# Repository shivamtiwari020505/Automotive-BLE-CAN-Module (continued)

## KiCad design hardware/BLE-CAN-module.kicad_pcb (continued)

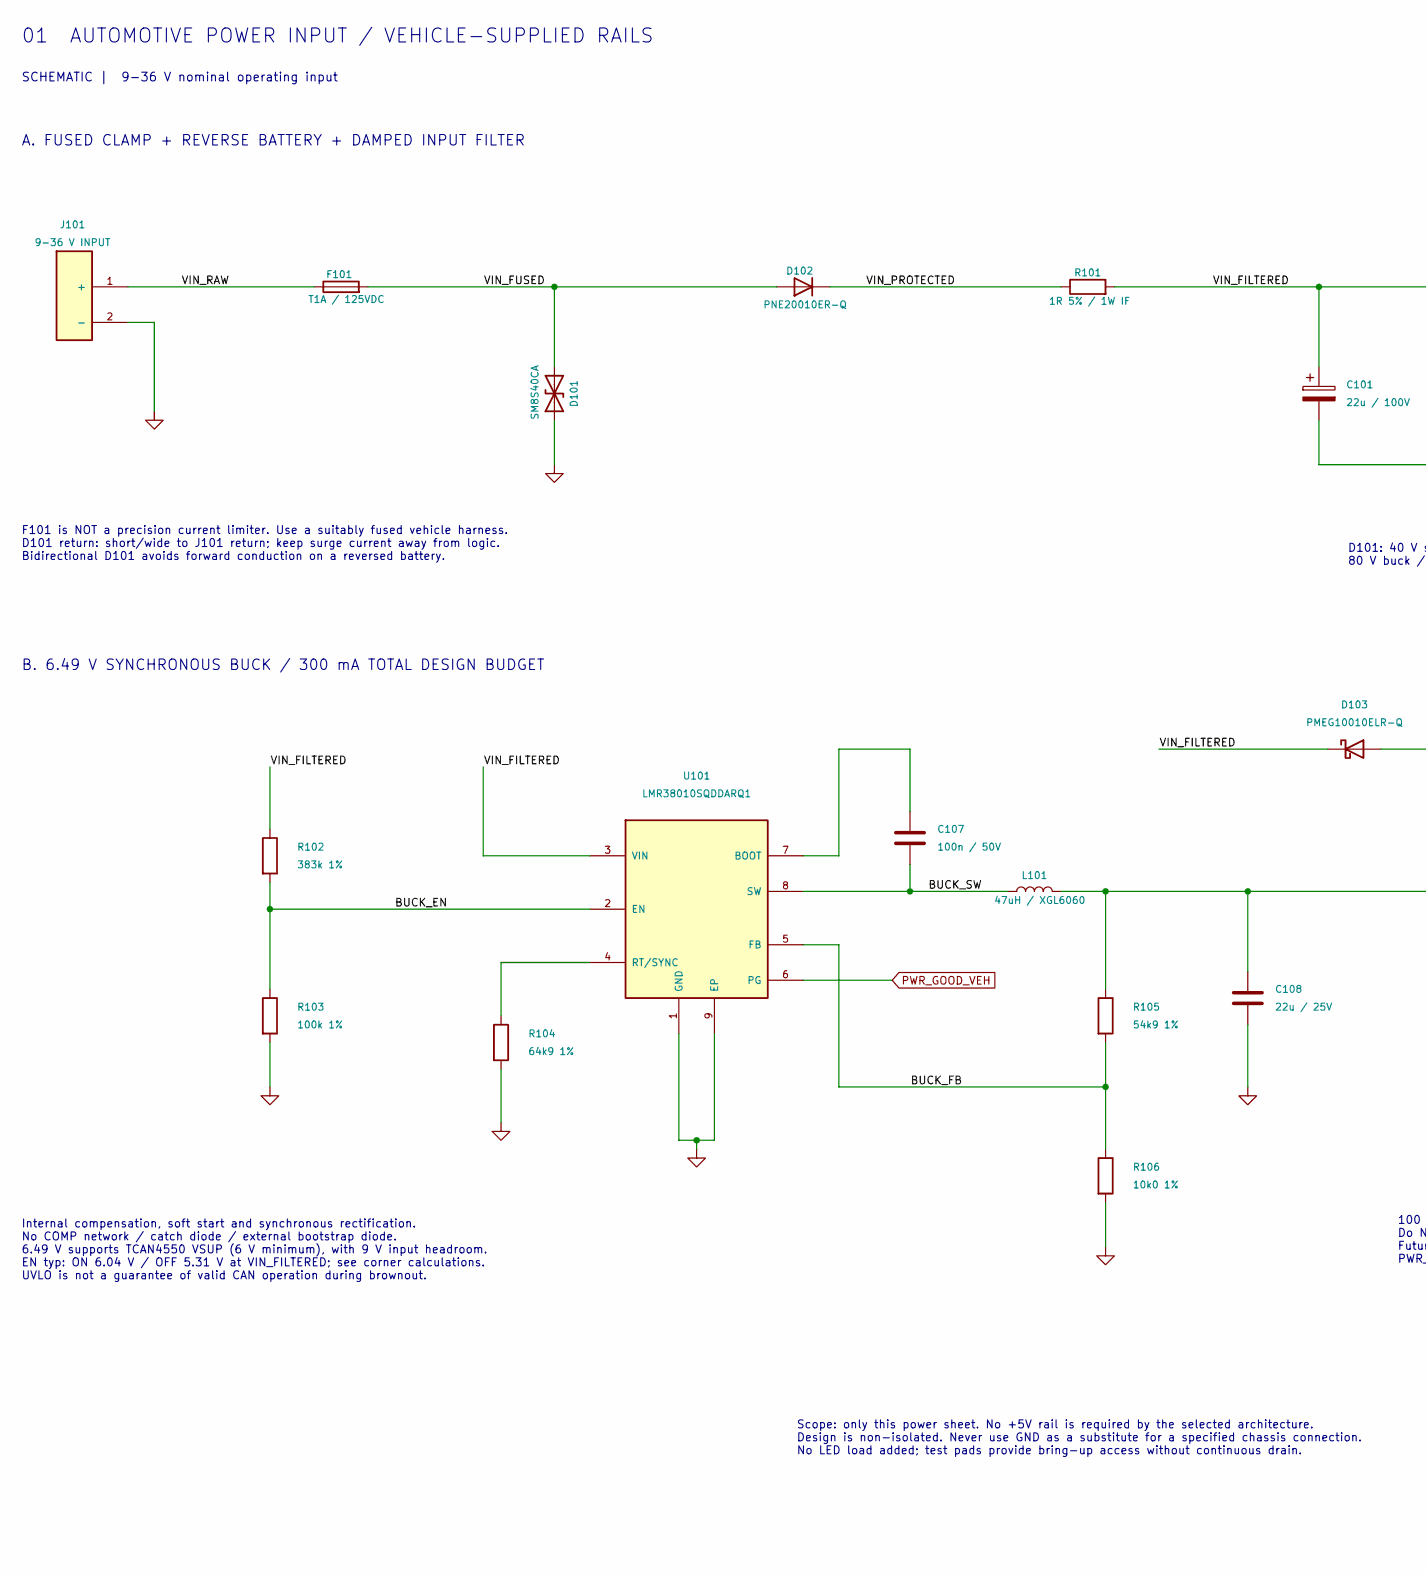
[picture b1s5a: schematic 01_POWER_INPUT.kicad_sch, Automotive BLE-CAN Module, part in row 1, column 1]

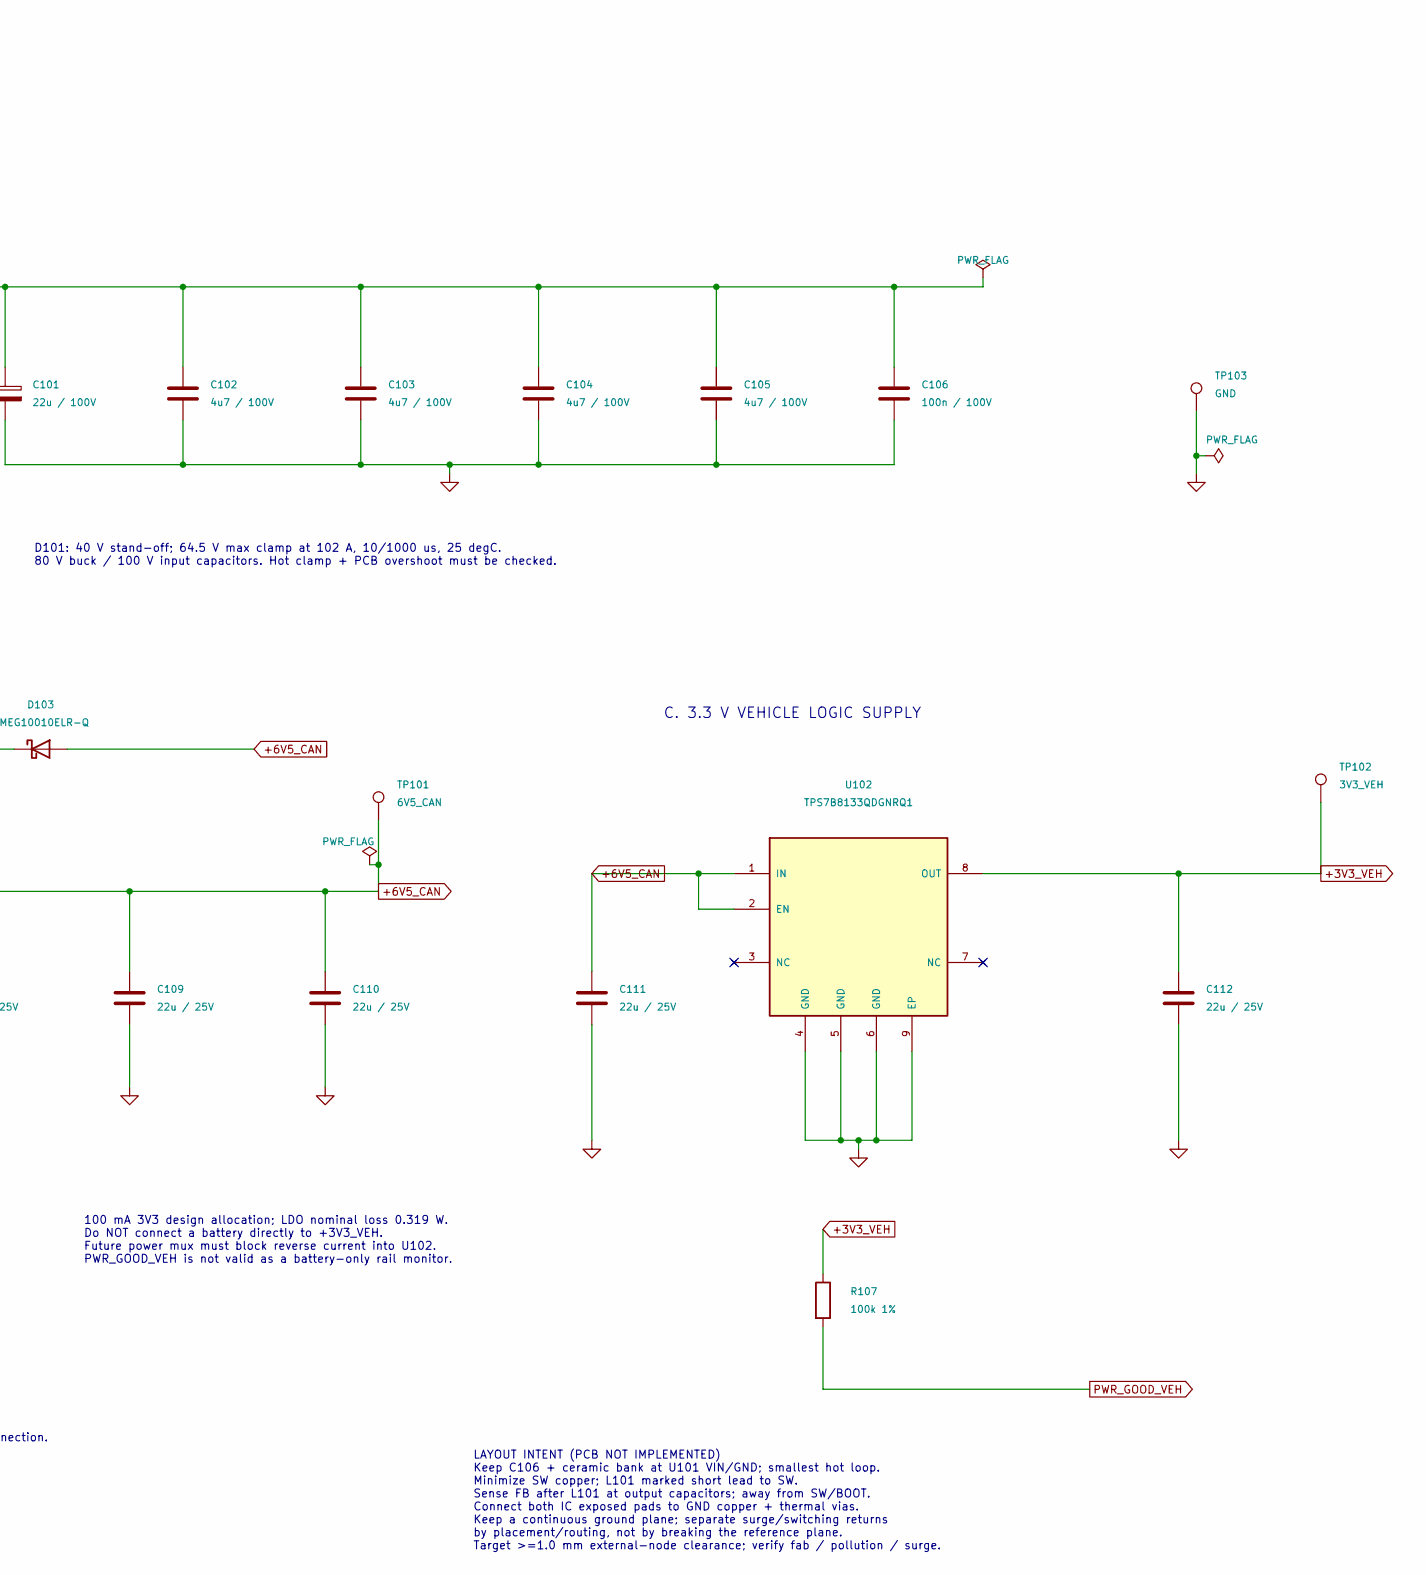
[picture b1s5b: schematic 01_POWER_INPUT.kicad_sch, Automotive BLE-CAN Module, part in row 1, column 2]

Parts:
C101: 22u / 100V; Panasonic_FK_F_8x10.2; MPN EEEFK2A220P
C102, C103, C104, C105: 4u7 / 100V; C_1206_3216Metric; MPN CGA5L1X7R2A475K160AC
C106: 100n / 100V; C_0805_2012Metric; MPN CGA4J2X7R2A104K125AA
C107: 100n / 50V; C_0603_1608Metric; MPN CGA3E2X7R1H104K080AA
C108, C109, C110, C111, C112: 22u / 25V; C_1210_3225Metric; MPN CGA6P3X7R1E226M250AB
D101: SM8S40CA; Vishay_DO-218AC_SM8S; MPN SM8S40CAHM3_A/I
D102: PNE20010ER-Q; Nexperia_CFP3_SOD-123W; MPN PNE20010ER-QX
D103: PMEG10010ELR-Q; Nexperia_CFP3_SOD-123W; MPN PMEG10010ELR-QX
F101: T1A / 125VDC; Fuse_Schurter_UMT250; MPN 3403.0166.24
J101: 9-36 V INPUT; TerminalBlock_Phoenix_MPT-0,5-2-2.54_1x02_P2.54mm_Horizontal; MPN 1725656
L101: 47uH / XGL6060; Coilcraft_XGL6060; MPN XGL6060-473MEC
R101: 1R 5% / 1W IF; R_2512_6332Metric; MPN CRCW25121R00JNEGIF
R102: 383k 1%; R_0603_1608Metric; MPN CRCW0603383KFKEA
R103, R107: 100k 1%; R_0603_1608Metric; MPN CRCW0603100KFKEA
R104: 64k9 1%; R_0603_1608Metric; MPN CRCW060364K9FKEA
R105: 54k9 1%; R_0603_1608Metric; MPN CRCW060354K9FKEA
R106: 10k0 1%; R_0603_1608Metric; MPN CRCW060310K0FKEA
TP101: 6V5_CAN; TestPoint_Pad_D2.0mm; MPN N/A - PCB copper pad
TP102: 3V3_VEH; TestPoint_Pad_D2.0mm; MPN N/A - PCB copper pad
TP103: GND; TestPoint_Pad_D2.0mm; MPN N/A - PCB copper pad
U101: LMR38010SQDDARQ1; TI_DDA0008B_PowerPAD; MPN LMR38010SQDDARQ1
U102: TPS7B8133QDGNRQ1; TI_DGN0008G_PowerPAD; MPN TPS7B8133QDGNRQ1

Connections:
+3V3_VEH: C112.1, R107.1, TP102.1 (1_1), U102.8 (OUT); also elsewhere on the board
+6V5_CAN: C108.1, C109.1, C110.1, C111.1, D103.2 (A), L101.2, R105.1, TP101.1 (1_1), U102.1 (IN), U102.2 (EN); also elsewhere on the board
/01_POWER_INPUT/BUCK_EN: R102.2, R103.1, U101.2 (EN)
/01_POWER_INPUT/BUCK_FB: R105.2, R106.1, U101.5 (FB)
/01_POWER_INPUT/BUCK_SW: C107.2, L101.1, U101.8 (SW)
/01_POWER_INPUT/VIN_FILTERED: C101.1, C102.1, C103.1, C104.1, C105.1, C106.1, D103.1 (K), R101.2, R102.1, U101.3 (VIN)
/01_POWER_INPUT/VIN_FUSED: D101.2 (A2), D102.2 (A), F101.2
/01_POWER_INPUT/VIN_PROTECTED: D102.1 (K), R101.1
/01_POWER_INPUT/VIN_RAW: F101.1, J101.1 (+)
GND: C101.2, C102.2, C103.2, C104.2, C105.2, C106.2, C108.2, C109.2, C110.2, C111.2, C112.2, D101.1 (A1), J101.2 (-), R103.2, R104.2, R106.2, TP103.1 (1_1), U101.1 (GND), U101.9 (EP), U102.4 (GND), U102.5 (GND), U102.6 (GND), U102.9 (EP); also elsewhere on the board
unnamed: C107.1, U101.7 (BOOT)
unnamed: R104.1, U101.4 (RT/SYNC)
PWR_GOOD_VEH: R107.2, U101.6 (PG)

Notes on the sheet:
SCHEMATIC | 9-36 V nominal operating input
LAYOUT INTENT (PCB NOT IMPLEMENTED) Keep C106 + ceramic bank at U101 VIN/GND; smallest hot loop. Minimize SW copper; L101 marked short lead to SW. Sense FB after L101 at output capacitors; away from SW/BOOT. Connect both IC exposed pads to GND copper + thermal vias. Keep a continuous ground plane; 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
100 mA 3V3 design allocation; LDO nominal loss 0.319 W. Do NOT connect a battery directly to +3V3_VEH. Future power mux must block reverse current into U102. PWR_GOOD_VEH is not valid as a battery-only rail monitor.
A. FUSED CLAMP + REVERSE BATTERY + DAMPED INPUT FILTER
Internal compensation, soft start and synchronous rectification. No COMP network / catch diode / external bootstrap diode. 6.49 V supports TCAN4550 VSUP (6 V minimum), with 9 V input headroom. EN typ: ON 6.04 V / OFF 5.31 V at VIN_FILTERED; see corner calculations. UVLO is not a guarantee of valid 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
Scope: only this power sheet. No +5V rail is required by the selected architecture. Design is non-isolated. Never use GND as a substitute for a specified chassis connection. No LED load added; test pads provide bring-up access without continuous drain.
F101 is NOT a precision current limiter. Use a suitably fused vehicle harness. D101 return: short/wide to J101 return; keep surge current away from logic. Bidirectional D101 avoids forward conduction on a reversed battery.
D101: 40 V stand-off; 64.5 V max clamp at 102 A, 10/1000 us, 25 degC. 80 V buck / 100 V input capacitors. Hot clamp + PCB overshoot must be checked.
C. 3.3 V VEHICLE LOGIC SUPPLY
B. 6.49 V SYNCHRONOUS BUCK / 300 mA TOTAL DESIGN BUDGET
01 AUTOMOTIVE POWER INPUT / VEHICLE-SUPPLIED RAILS

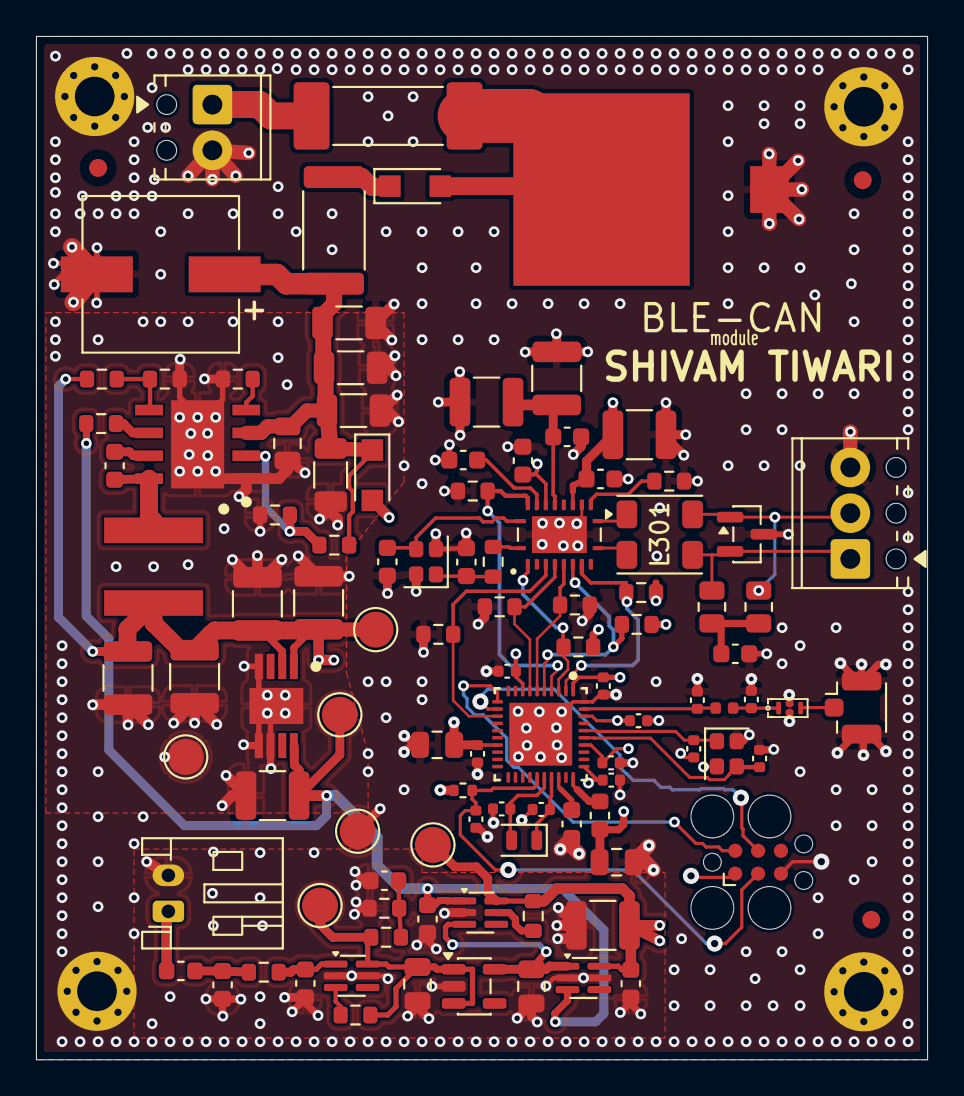
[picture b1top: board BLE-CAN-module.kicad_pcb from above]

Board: 4 copper layers, 49.5 x 56.8 mm, 110 parts (0 on the bottom side), 53 nets.
